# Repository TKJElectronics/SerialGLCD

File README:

The code is released under the GNU General Public License.

This is the firmware and PCB for the SerialGLCD board by Kristian Lauszus, TKJ Electronics 2012.

For it to work move ks0108_Arduino.h into the glcd library folder like so: Arduino/libraries/glcd/config/ks0108_Arduino.h
Also remember to solder the solderjumper according to your Pinout (see http://www.arduino.cc/playground/Code/GLCDks0108).
The glcd library can be found at the following link: http://code.google.com/p/glcd-arduino/

For more information see my blog at http://blog.tkjelectronics.dk/ or send me an email at kristianl at tkjelectronics dot dk.

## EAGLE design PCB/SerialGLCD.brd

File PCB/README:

The Gerber files are for ordering at http://www.dorkbotpdx.org/wiki/pcb_order

For more information see my blog at http://blog.tkjelectronics.dk/ or send me an email at kristianl at tkjelectronics dot dk.

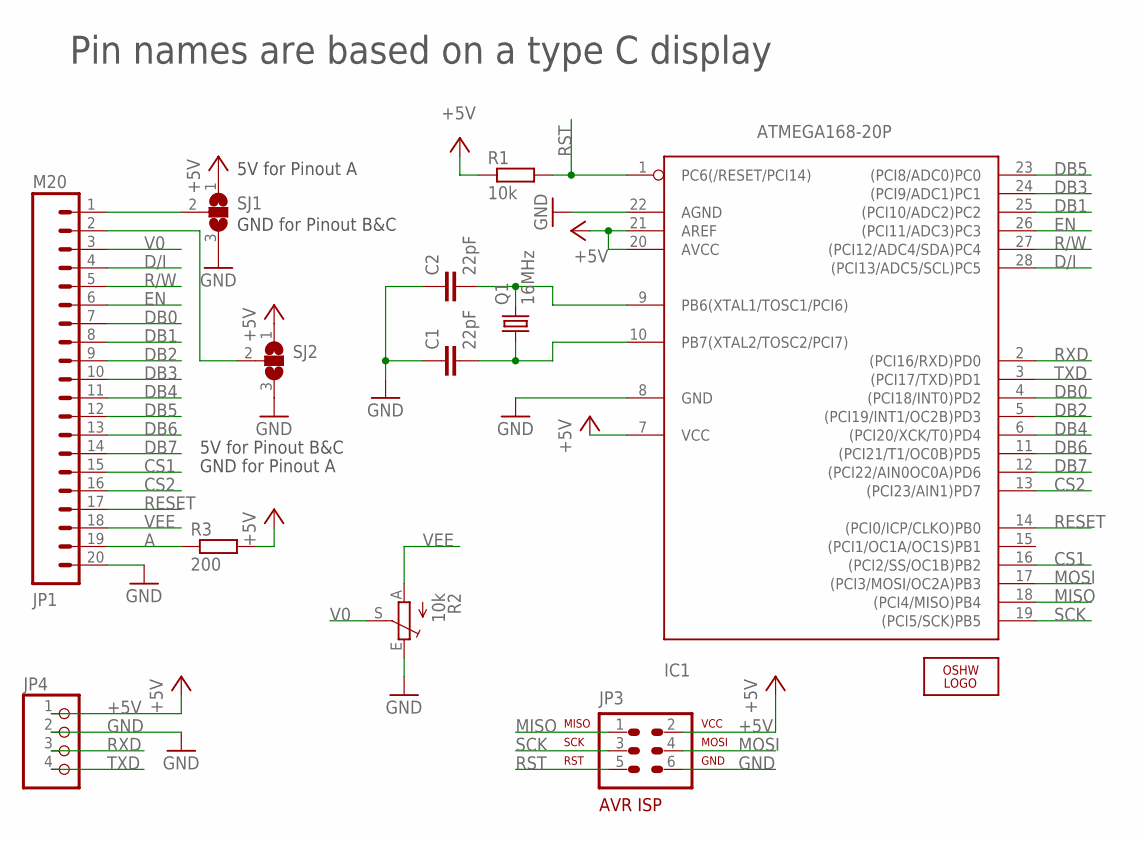
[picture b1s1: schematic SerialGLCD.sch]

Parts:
C1, C2: 22pF; C025-024X044
IC1: ATMEGA168-20P; DIL28-3
JP1: M20; 1X20
JP3: AVR-ISP-6VERT; AVR-ISP-6
JP4: PINHD-1X4/90; 1X04/90
LOGO1: OSHW_LOGO_FILLX0100-NT; OSHW_FILLX100_NOTEXT
Q1: 16MHz; HC49U-V
R1: 10k; 0207/10
R2: 10k; B25P
R3: 200; 0207/10
SJ1, SJ2: SJ2W; SJ_2

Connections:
+5V: IC1.7 (VCC), IC1.20 (AVCC), IC1.21 (AREF), JP3.2, JP4.1, R1.1, R3.2, SJ1.1, SJ2.1
A: JP1.19, R3.1
CS1: IC1.16 ((PCI2/SS/OC1B)PB2), JP1.15
CS2: IC1.13 ((PCI23/AIN1)PD7), JP1.16
D/I: IC1.28 ((PCI13/ADC5/SCL)PC5), JP1.4
DB0: IC1.4 ((PCI18/INT0)PD2), JP1.7
DB1: IC1.25 ((PCI10/ADC2)PC2), JP1.8
DB2: IC1.5 ((PCI19/INT1/OC2B)PD3), JP1.9
DB3: IC1.24 ((PCI9/ADC1)PC1), JP1.10
DB4: IC1.6 ((PCI20/XCK/T0)PD4), JP1.11
DB5: IC1.23 ((PCI8/ADC0)PC0), JP1.12
DB6: IC1.11 ((PCI21/T1/OC0B)PD5), JP1.13
DB7: IC1.12 ((PCI22/AIN0OC0A)PD6), JP1.14
EN: IC1.26 ((PCI11/ADC3)PC3), JP1.6
GND: C1.1, C2.1, IC1.8 (GND), IC1.22 (AGND), JP1.20, JP3.6, JP4.2, R2.E, SJ1.3, SJ2.3
MISO: IC1.18 ((PCI4/MISO)PB4), JP3.1
MOSI: IC1.17 ((PCI3/MOSI/OC2A)PB3), JP3.4
unnamed: JP1.1, SJ1.2
unnamed: JP1.2, SJ2.2
unnamed: C2.2, IC1.9 (PB6(XTAL1/TOSC1/PCI6)), Q1.2
unnamed: C1.2, IC1.10 (PB7(XTAL2/TOSC2/PCI7)), Q1.1
R/W: IC1.27 ((PCI12/ADC4/SDA)PC4), JP1.5
RESET: IC1.14 ((PCI0/ICP/CLKO)PB0), JP1.17
RST: IC1.1 (PC6(/RESET/PCI14)), JP3.5, R1.2
RXD: IC1.2 ((PCI16/RXD)PD0), JP4.3
SCK: IC1.19 ((PCI5/SCK)PB5), JP3.3
TXD: IC1.3 ((PCI17/TXD)PD1), JP4.4
V0: JP1.3, R2.S
VEE: JP1.18, R2.A

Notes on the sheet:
5V for Pinout A
GND for Pinout B&C
5V for Pinout B&C
GND for Pinout A
Pin names are based on a type C display

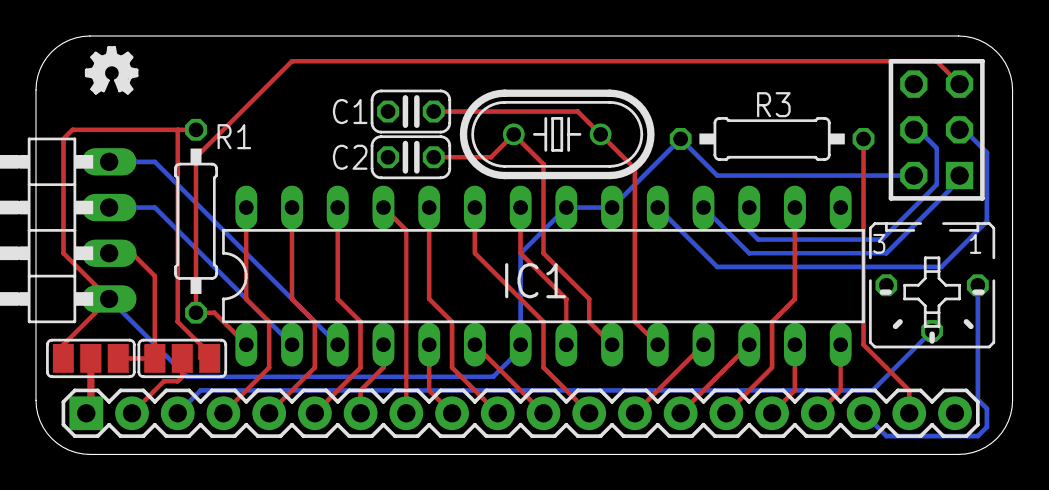
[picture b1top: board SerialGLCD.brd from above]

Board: 2 copper layers, 54.3 x 23.2 mm, 13 parts (0 on the bottom side), 29 nets.

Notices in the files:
parts and their libraries:
SparkFun: Licensing: CC v3.0 Share-Alike You are welcome to use this library for commercial purposes.
